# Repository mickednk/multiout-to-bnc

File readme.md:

# Multiout to BNC
The Console to BNC is a small project I put together to solve my snakepit of cables behind my consoles and Extron Crosspoint.
this PCB board is the main part of the project and doesnt need to be used with BNC connectors, you can use it in combination with a SCART connector or regular RCA connectors. the purpose of the PCB is to move the components closer to the console.

## SNES to BNC
This PCB is designed to be used with a NTSC SNES console, it will work with both a US SNES and a Japanese Super Famicom.
It will also work with a NESRGB modified NES if it uses an multiout connector like the AV Famicom does.
It might be compatible with other multiout consoles but it is designed with the NTSC SNES in mind.

### Parts needed
| Mouser part number    | Quantity  | Description                   | Designation |
| :---                  | :---:     | :---                          | :---        |
| 81-GRM31CR60J227ME1K  | 3         | 220uF capacitory 1206 package | C1, C2, C3  |

## Gamecube to BNC
This PCB is designed to be used with a PAL Gamecube ONLY.
It will not work with an NTSC Gamecube because they don't output RGB and I am pretty sure it would damage the monitor that you connect to.

### Parts needed
| Mouser part number    | Quantity  | Description                   | Designation   |
| :---                  | :---:     | :---                          | :---          |
| 81-GRM31CR60J227ME1K  | 3         | 220uF capacitor 1206 package  | C1, C2, C3    |
| 581-06036C104KAT2A    | 2         | 0.1uF capacitor 603 package   | C4, C5        |
| 71-CRCW0603680KFKEAC  | 1         | 680KOhm resistor 603 package  | R1            |
| 71-CRCW060375R0FKEAC  | 1         | 75Ohm resistor 603 package    | R2            |
| 926-LM1881MX/NOPB     | 1         | LM1881 Sync seperator circuit | U2            |

## PS2 to BNC
This PCB is designed to be used with Playstation 2 ONLY, it wont work with PS1 because it needs caps on the RGB lines to be compatible with PS1.

### Parts needed
| Mouser part number    | Quantity  | Description                   | Designation   |
| :---                  | :---:     | :---                          | :---          |
| 581-06036C104KAT2A    | 2         | 0.1uF capacitor 603 package   | C1, C2        |
| 71-CRCW0603680KFKEAC  | 1         | 680KOhm resistor 603 package  | R1            |
| 926-LM1881MX/NOPB     | 1         | LM1881 Sync seperator circuit | U1            |

## Connectors
### Nintendo consoles
The PCB is designed to use the knock off multiout connector that can be found at Console5.com (https://console5.com/store/nintendo-snes-super-famicom-n64-av-multi-out-plug-for-custom-rgb-cables-repair.html)
I have seen it on Aliexpress as well so it shouldn't be to difficult to find.

### Playstation consoles
The PCB is designed to use the knock off multiout connector that can be found at Console5.com (https://console5.com/store/sony-playstation-1-2-ps1-ps2-av-multi-out-plug-for-custom-rgb-cables-repair.html)
I have seen it on Aliexpress as well so it shouldn't be to difficult to find.

# Contribute to the project
I am not an electrical engineer so I have probably made tons of mistakes when routing and such, there is probably even more errors on the Gamecube one. With that said you are welcome to contribute by doing pull requests to this repository. I have taken this project as far as I need it but I can see how someone might want to build one for the PAL SNES or the N64.

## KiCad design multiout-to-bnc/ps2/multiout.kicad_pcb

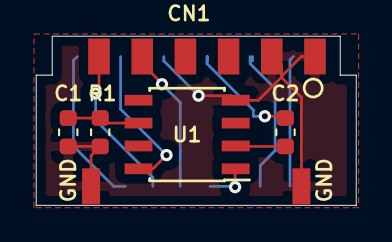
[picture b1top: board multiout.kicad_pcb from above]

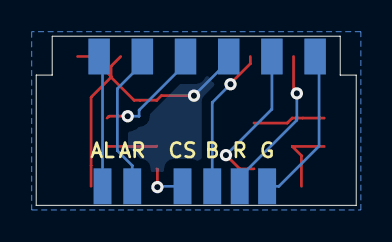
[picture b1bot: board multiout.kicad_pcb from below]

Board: 2 copper layers, 17.8 x 9.4 mm, 13 parts (6 on the bottom side), 11 nets.

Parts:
AL: L; WIREPAD
AR: R; WIREPAD
B: B; WIREPAD
C1, C2: 0.1uF; C_0603_1608Metric
CN1: AVCONNECTOR
CS: CS; WIREPAD
G: G; WIREPAD
GND: GND; WIREPAD
GND#2: GND; WIREPAD
R: R; WIREPAD
R1: 680k; R_0603_1608Metric
U1: LM1881; SOIC-8_3.9x4.9mm_P1.27mm

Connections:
GND: C1.1, CN1.1, CN1.3, CN1.8, GND.1, GND#2.1, R1.1, U1.4
unnamed: C1.2, R1.2, U1.6
unnamed: C2.1, CN1.6
unnamed: C2.2, U1.2
unnamed: AL.1, CN1.2
unnamed: AR.1, CN1.4
unnamed: B.1, CN1.9
unnamed: CN1.11, R.1
unnamed: CN1.12, G.1
unnamed: CS.1, U1.1
VCC: CN1.10, U1.8

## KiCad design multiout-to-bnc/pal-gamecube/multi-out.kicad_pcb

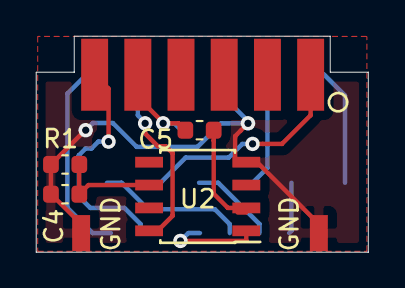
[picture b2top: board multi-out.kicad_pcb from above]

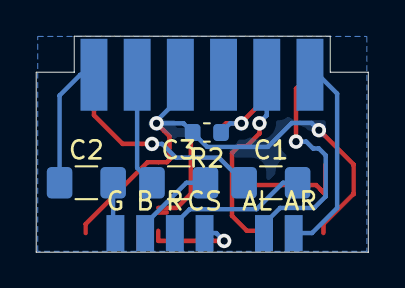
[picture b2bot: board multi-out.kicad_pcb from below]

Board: 2 copper layers, 18.4 x 12.0 mm, 17 parts (10 on the bottom side), 14 nets.

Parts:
AL: L; WIREPAD
AR: R; WIREPAD
B: B; WIREPAD
C1, C2, C3: 220uF; C_1206_3216Metric_Pad1.42x1.75mm_HandSolder
C4, C5: 0.1uF; C_0603_1608Metric
CS: CS; WIREPAD
G: G; WIREPAD
GND: GND; WIREPAD
GND#2: GND; WIREPAD
R: R; WIREPAD
R1: 680k; R_0603_1608Metric
R2: 75k; R_0603_1608Metric
U1: AV-CONNECTOR; AVCON
U2: LM1881; SOIC-8_3.9x4.9mm_P1.27mm

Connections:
GND: C4.1, GND.1, GND#2.1, R1.1, R2.2, U1.5, U1.6, U2.4
unnamed: C1.1, U1.1
unnamed: C1.2, R.1
unnamed: C2.1, U1.2
unnamed: C2.2, G.1
unnamed: C3.1, U1.4
unnamed: B.1, C3.2
unnamed: C4.2, R1.2, U2.6
unnamed: C5.1, R2.1, U1.9
unnamed: C5.2, U2.2
unnamed: CS.1, U2.1
unnamed: AR.1, U1.12
unnamed: AL.1, U1.11
unnamed: U1.10, U2.8

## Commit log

2019-05-01 Add project for SNES PCB
    This one will also work with NESRGB modified NES.
2019-05-01 Add project for PAL Gamecube PCB
2019-09-01 Add 75 Ohm resistor between composite line and ground
2020-01-31 Add readme with information and instructions on the PCB
2020-02-16 Add new project for PS2 to BNC
2020-02-16 Add schematic symbol for the multiout connector
2020-02-19 Add footprint for multiout connector
2020-02-19 Add schematic layout of the board
2020-02-19 Assign footprint to schema symbols
2020-02-19 Add outline to edge cut layer
2020-02-19 Add footprint of the wirepad
2020-02-19 Add design rules and layer rules
2020-02-19 Add routes to pcb
2020-03-22 Update footprint of connector
2020-03-22 Reroute after design changes to connector
2020-03-29 Updated Readme file
2020-11-10 Corrected placement of edge connector.
